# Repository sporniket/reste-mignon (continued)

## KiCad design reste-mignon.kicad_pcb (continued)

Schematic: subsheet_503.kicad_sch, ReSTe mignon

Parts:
C500, C501, C502, C511, C512, C513, C514, C523, C565: 0.1uF; C_1206_3216Metric_Pad1.33x1.80mm_HandSolder
C505, C506, C509, C510, C517, C518, C521, C522: 0.001uF; C_1206_3216Metric_Pad1.33x1.80mm_HandSolder
C2601: 0.33uF; C_1206_3216Metric_Pad1.33x1.80mm_HandSolder
CP508, CP520, CP566, CP567: 47uF; C_Radial_D6.3mm_H11.0mm_P2.50mm
CP564: 100uF; C_Radial_D8.0mm_H11.5mm_P3.50mm
Q500: UA78L08; TO-92L_Inline_Wide
R501, R502, R503, R504, R510, R511, R512, R513: 10K 1%; R_1206_3216Metric_Pad1.30x1.75mm_HandSolder
R507, R516: 1K8 1%; R_1206_3216Metric_Pad1.30x1.75mm_HandSolder
R545, R546: 100K 1%; R_1206_3216Metric_Pad1.30x1.75mm_HandSolder
U504, U507: LF347N_mu; DIP-14_W7.62mm_LongPads
U505, U506: MF4CN-100_PHY; DIP-8_W7.62mm_LongPads

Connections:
+8.2V: C500.1, C565.1, CP564.1, Q500.1 (VO), U504.4 (V+); also elsewhere on the board
/U504~~U507 — Sound amp. & filter/+12V: C2601.1, Q500.3 (VI)
ASOUND_LEFT: CP508.1; also elsewhere on the board
ASOUND_RIGHT: CP520.1; also elsewhere on the board
DAC_LEFT: U504.3 (IN1+); also elsewhere on the board
DAC_RIGHT: U504.12 (IN4+); also elsewhere on the board
FCLK: U505.2 (CLK_R), U506.2 (CLK_R); also elsewhere on the board
GIL: R507.2; also elsewhere on the board
GIR: R516.2; also elsewhere on the board
GND: C500.2, C501.2, C502.2, C509.2, C510.2, C511.1, C512.1, C513.1, C514.2, C521.2, C522.2, C523.1, C565.2, C2601.2, CP564.2, Q500.2 (GND), R545.2, R546.2, U505.3 (L.Sh), U505.6 (AGND), U506.3 (L.Sh), U506.6 (AGND), U507.3 (IN1+), U507.5 (IN2+), U507.10 (IN3+), U507.12 (IN4+); also elsewhere on the board
unnamed: CP566.1, U504.1 (OUT1), U504.2 (IN1-)
unnamed: CP567.1, U504.13 (IN4-), U504.14 (OUT4)
unnamed: CP566.2, R545.1, U505.8 (FILTER_IN)
unnamed: R503.2, U505.5 (FILTER_OUT)
unnamed: CP567.2, R546.1, U506.8 (FILTER_IN)
unnamed: R512.2, U506.5 (FILTER_OUT)
unnamed: C505.2, C509.1, R501.2, R503.1, U507.2 (IN1-)
unnamed: C505.1, R501.1, R504.2, U507.1 (OUT1)
unnamed: C517.2, C521.1, R510.2, R512.1, U507.6 (IN2-)
unnamed: C517.1, R510.1, R513.2, U507.7 (OUT2)
unnamed: C518.2, C522.1, R511.2, R513.1, R516.1, U507.9 (IN3-)
unnamed: C518.1, CP520.2, R511.1, U507.8 (OUT3)
unnamed: C506.2, C510.1, R502.2, R504.1, R507.1, U507.13 (IN4-)
unnamed: C506.1, CP508.2, R502.1, U507.14 (OUT4)
V_AUD+: C501.1, C502.1, C514.1, U505.7 (V+), U506.7 (V+), U507.4 (V+); also elsewhere on the board
V_AUD-: C511.2, C512.2, C513.2, C523.2, U504.11 (V-), U505.4 (V-), U506.4 (V-), U507.11 (V-); also elsewhere on the board

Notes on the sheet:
Use 1% resistors
Alternatives for Q500, TO-92-3 : STMicroelectronics L78L08 / Onsemi MC78L08 / Texas instrument UA78L08
for U507
for U504
for U505
for U506
Ground plane this area

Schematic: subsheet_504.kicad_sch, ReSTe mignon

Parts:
C524, C536: 0.1uF; C_1206_3216Metric_Pad1.33x1.80mm_HandSolder
C528, C531, C534, C538: 0.0082uF; C_1206_3216Metric_Pad1.33x1.80mm_HandSolder
CP525, CP529, CP535, CP537, CP541, CP543, CP544, CP546, CP547: 47uF; C_Radial_D6.3mm_H11.0mm_P2.50mm
CP542: 10uF; C_Radial_D5.0mm_H11.0mm_P2.00mm
J502: Phono LEFT; socket-rca-5-pins
J503: Phono RIGHT; socket-rca-5-pins
R520, R533, R540, R541: 1K; R_1206_3216Metric_Pad1.30x1.75mm_HandSolder
R524, R537: 3K6; R_1206_3216Metric_Pad1.30x1.75mm_HandSolder
R525, R527, R530, R538, R2701: 10K; R_1206_3216Metric_Pad1.30x1.75mm_HandSolder
R531, R539: 51K; R_1206_3216Metric_Pad1.30x1.75mm_HandSolder
R590, R591: 270K; R_1206_3216Metric_Pad1.30x1.75mm_HandSolder
U504: LF347N_mu; DIP-14_W7.62mm_LongPads
U508: LMC1992CCN_PHY; DIP-28_W15.24mm_LongPads

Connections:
+8.2V: C524.1, R525.1, U508.28 (V+); also elsewhere on the board
/U508 — Sound mix and output/audio_full: CP541.1, CP546.1, R531.1, U508.4 (LEFT_INPUT1), U508.26 (RIGHT_INPUT1)
/U508 — Sound mix and output/audio_low: R525.2, R531.2, R539.2, R2701.1, U508.5 (LEFT_INPUT2), U508.25 (RIGHT_INPUT2)
/U508 — Sound mix and output/left_op_amp_out: C531.1, U508.12 (LEFT_OP_AMP_OUT)
/U508 — Sound mix and output/left_tone_out: C531.2, U508.11 (LEFT_TONE_OUT)
/U508 — Sound mix and output/right_op_amp_out: C534.1, U508.18 (RIGHT_OP_AMP_OUT)
/U508 — Sound mix and output/right_tone_out: C534.2, U508.19 (RIGHT_TONE_OUT)
ASOUND_LEFT: C528.1, U508.9 (LEFT_SELECT_IN); also elsewhere on the board
ASOUND_RIGHT: C538.1, U508.21 (RIGHT_SELECT_IN); also elsewhere on the board
AUDIO: R540.1, R541.1; also elsewhere on the board
AUDIOI: CP546.2; also elsewhere on the board
AUDIOS: CP541.2; also elsewhere on the board
GIL: CP544.2; also elsewhere on the board
GIR: CP547.2; also elsewhere on the board
GND: C524.2, C536.2, CP535.2, CP542.2, J502.2 (Ext), J503.2 (Ext), R530.2, R590.2, R591.2, U504.5 (IN2+), U504.10 (IN3+), U508.15 (GND); also elsewhere on the board
MWD: U508.1 (DATA); also elsewhere on the board
MWK: U508.2 (CLOCK); also elsewhere on the board
unnamed: C536.1, CP535.1, R530.1, R539.1, R2701.2
unnamed: CP525.1, R520.1
unnamed: CP529.2, R527.2
unnamed: CP537.1, R533.1
unnamed: CP543.2, R538.2
unnamed: CP525.2, J502.1 (In), R590.1
unnamed: CP537.2, J503.1 (In), R591.1
unnamed: R524.2, R527.1, U504.6 (IN2-)
unnamed: R524.1, R540.2, U504.7 (OUT2)
unnamed: R537.2, R538.1, U504.9 (IN3-)
unnamed: R537.1, R541.2, U504.8 (OUT3)
unnamed: CP542.1, U508.27 (BYPASS)
unnamed: CP529.1, R520.2, U508.14 (LEFT_FRONT_OUT)
unnamed: CP544.1, U508.8 (LEFT_SELECT_OUT)
unnamed: C528.2, U508.10 (LEFT_TONE_IN)
unnamed: CP543.1, R533.2, U508.16 (RIGHT_FRONT_OUT)
unnamed: CP547.1, U508.22 (RIGHT_SELECT_OUT)
unnamed: C538.2, U508.20 (RIGHT_TONE_IN)
XMWE: U508.3 (~ENABLE); also elsewhere on the board

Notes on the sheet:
To Video port
Ground plane this area
From Video port
From YM2149
LMC Mixer Fix The original circuit gives no sound at 'audio_low', instead of a -12 dB attenuated sound to have a balanced mix of digitized sound and sound from YM2149. Peter Putnik did some research on that problem and proposed the following fix : - Cut between R531 and R539/R530, to insert a 10K r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

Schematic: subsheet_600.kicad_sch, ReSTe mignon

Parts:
C633, C634, C635, C636: 0.22uF; C_1206_3216Metric_Pad1.33x1.80mm_HandSolder
CP600: 100uF; C_Radial_D8.0mm_H11.5mm_P3.50mm
U600, U601, U602, U603: SIMM_30_PHY; socket-simm-30-P2.54mm

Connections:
GND: C633.2, C634.2, C635.2, C636.2, CP600.2, U600.9 (GND), U600.22 (GND), U601.9 (GND), U601.22 (GND), U602.9 (GND), U602.22 (GND), U603.9 (GND), U603.22 (GND); also elsewhere on the board
MADDR0: U600.4 (A0), U601.4 (A0), U602.4 (A0), U603.4 (A0); also elsewhere on the board
MADDR1: U600.5 (A1), U601.5 (A1), U602.5 (A1), U603.5 (A1); also elsewhere on the board
MADDR2: U600.7 (A2), U601.7 (A2), U602.7 (A2), U603.7 (A2); also elsewhere on the board
MADDR3: U600.8 (A3), U601.8 (A3), U602.8 (A3), U603.8 (A3); also elsewhere on the board
MADDR4: U600.11 (A4), U601.11 (A4), U602.11 (A4), U603.11 (A4); also elsewhere on the board
MADDR5: U600.12 (A5), U601.12 (A5), U602.12 (A5), U603.12 (A5); also elsewhere on the board
MADDR6: U600.14 (A6), U601.14 (A6), U602.14 (A6), U603.14 (A6); also elsewhere on the board
MADDR7: U600.15 (A7), U601.15 (A7), U602.15 (A7), U603.15 (A7); also elsewhere on the board
MADDR8: U600.17 (A8), U601.17 (A8), U602.17 (A8), U603.17 (A8); also elsewhere on the board
MADDR9: U600.18 (A9), U601.18 (A9), U602.18 (A9), U603.18 (A9); also elsewhere on the board
MDATA0: U601.3 (DQ0), U603.3 (DQ0); also elsewhere on the board
MDATA1: U601.6 (DQ1), U603.6 (DQ1); also elsewhere on the board
MDATA2: U601.10 (DQ2), U603.10 (DQ2); also elsewhere on the board
MDATA3: U601.13 (DQ3), U603.13 (DQ3); also elsewhere on the board
MDATA4: U601.16 (DQ4), U603.16 (DQ4); also elsewhere on the board
MDATA5: U601.20 (DQ5), U603.20 (DQ5); also elsewhere on the board
MDATA6: U601.23 (DQ6), U603.23 (DQ6); also elsewhere on the board
MDATA7: U601.25 (DQ7), U603.25 (DQ7); also elsewhere on the board
MDATA8: U600.3 (DQ0), U602.3 (DQ0); also elsewhere on the board
MDATA9: U600.6 (DQ1), U602.6 (DQ1); also elsewhere on the board
MDATA10: U600.10 (DQ2), U602.10 (DQ2); also elsewhere on the board
MDATA11: U600.13 (DQ3), U602.13 (DQ3); also elsewhere on the board
MDATA12: U600.16 (DQ4), U602.16 (DQ4); also elsewhere on the board
MDATA13: U600.20 (DQ5), U602.20 (DQ5); also elsewhere on the board
MDATA14: U600.23 (DQ6), U602.23 (DQ6); also elsewhere on the board
MDATA15: U600.25 (DQ7), U602.25 (DQ7); also elsewhere on the board
VCC: C633.1, C634.1, C635.1, C636.1, CP600.1, U600.1 (VCC), U600.30 (VCC), U601.1 (VCC), U601.30 (VCC), U602.1 (VCC), U602.30 (VCC), U603.1 (VCC), U603.30 (VCC); also elsewhere on the board
XCAS0H: U600.2 (~CAS); also elsewhere on the board
XCAS0L: U601.2 (~CAS); also elsewhere on the board
XCAS1H: U602.2 (~CAS); also elsewhere on the board
XCAS1L: U603.2 (~CAS); also elsewhere on the board
XRAS0: U600.27 (~RAS), U601.27 (~RAS); also elsewhere on the board
XRAS1: U602.27 (~RAS), U603.27 (~RAS); also elsewhere on the board
XWE: U600.21 (~WE), U601.21 (~WE), U602.21 (~WE), U603.21 (~WE); also elsewhere on the board

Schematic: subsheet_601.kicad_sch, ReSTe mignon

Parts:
C632: 0.1uF; C_1206_3216Metric_Pad1.33x1.80mm_HandSolder
E0, E1, E2, E3, E4, E5, E6, E7: SolderJumper_2_Open; SolderJumper-2_P1.3mm_Open_Pad1.0x1.5mm
RN2901, RN2902: 10K ×4; R_Array_Convex_4x0603
U632: 74LS244_PHY; DIP-20_W7.62mm_LongPads

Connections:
/E[0..7] — Jumper pads/e0: E0.2 (B), RN2901.1 (R1.1), U632.2 (1A1)
/E[0..7] — Jumper pads/e1: E1.2 (B), RN2901.2 (R2.1), U632.17 (2A4)
/E[0..7] — Jumper pads/e2: E2.2 (B), RN2901.3 (R3.1), U632.4 (1A2)
/E[0..7] — Jumper pads/e3: E3.2 (B), RN2901.4 (R4.1), U632.15 (2A3)
/E[0..7] — Jumper pads/e4: E4.2 (B), RN2902.1 (R1.1), U632.6 (1A3)
/E[0..7] — Jumper pads/e5: E5.2 (B), RN2902.2 (R2.1), U632.13 (2A2)
/E[0..7] — Jumper pads/e6: E6.2 (B), RN2902.3 (R3.1), U632.8 (1A4)
/E[0..7] — Jumper pads/e7: E7.2 (B), RN2902.4 (R4.1), U632.11 (2A1)
DATA8: U632.18 (1Y1); also elsewhere on the board
DATA9: U632.3 (2Y4); also elsewhere on the board
DATA10: U632.16 (1Y2); also elsewhere on the board
DATA11: U632.5 (2Y3); also elsewhere on the board
DATA12: U632.14 (1Y3); also elsewhere on the board
DATA13: U632.7 (2Y2); also elsewhere on the board
DATA14: U632.12 (1Y4); also elsewhere on the board
DATA15: U632.9 (2Y1); also elsewhere on the board
GND: C632.2, E0.1 (A), E1.1 (A), E2.1 (A), E3.1 (A), E4.1 (A), E5.1 (A), E6.1 (A), E7.1 (A), U632.10 (GND); also elsewhere on the board
VCC: C632.1, RN2901.5 (R4.2), RN2901.6 (R3.2), RN2901.7 (R2.2), RN2901.8 (R1.2), RN2902.5 (R4.2), RN2902.6 (R3.2), RN2902.7 (R2.2), RN2902.8 (R1.2), U632.20 (Vcc); also elsewhere on the board
XBUTTON: U632.1 (~1G), U632.19 (~2G); also elsewhere on the board

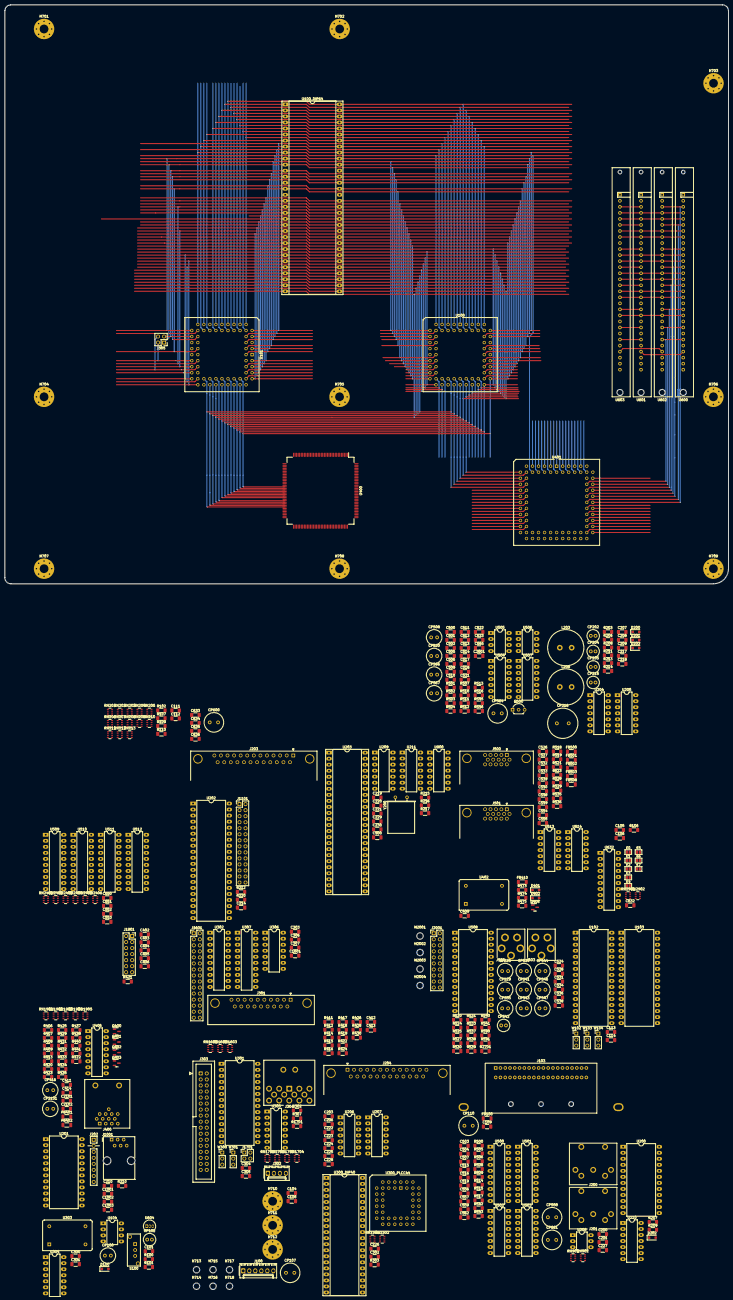
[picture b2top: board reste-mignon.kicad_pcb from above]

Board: 4 copper layers, 304.8 x 243.8 mm, 420 parts (0 on the bottom side), 492 nets.

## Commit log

2021-12-06 Removed T-filters
2021-12-08 Added DIP-64 CPU port extension
2021-12-09 removed the external blitter
2021-12-09 prepare to work publicly
2021-12-10 Resolves #1 : Use 4-resistor packs wherever it is possible
2021-12-21 annotate resistor networks and mark unused pins as unconnected
2021-12-21 Resolves #10 : Remove the C103
2021-12-21 Resolves #6 : Apply the reset fix
2021-12-21 Resolves #5 : Apply the fix for the video ghosting
2022-01-10 Resolves #7 : Assign SMD footprints to resistors pack
2022-01-11 Resolves #11 : Use the reference 'FB?' for the ferrite beads
2022-01-11 Resolves #12 : Use the reference 'CP?' for polarized capacitors
2022-02-09 Resolves #2 : apply the pull-up fix to data and address bus
2022-02-09 Resolves #3 : Apply the DMA Pull up fix on databus
2022-02-10 Resolves #4 : Apply the 1772 pull-up fix
2022-02-15 Resolves #18 : Apply the LMC mixer fix
2022-02-15 rename files as 'reste-mignon'
2022-02-16 Resolves #13 : assign 1206 hand-solder footprints to resistors
2022-02-16 Resolves #8 : Assign 1206 hand-solder footprints to non polarized capacitors
2022-03-16 Resolves #20 : Replace polarized capacitors CP101 and CP536 by unpolarized ones
2022-03-16 Resolves #9 : Assign radial THT footprints to polarized capacitors
2022-03-16 Resolves #14 : assign smd footprints for ferrite beads
2022-04-01 Resolves #16 : assign smd footprints to diodes
2022-04-01 Resolves #17 : assign smd footprints to transistors
2022-04-01 Resolves #21 : Change Q400 to Q405 from 2N3904 to MMBT3904
2022-04-01 Resolves #22 : Change Q500 from LM78L82 to UA78L08 -- add bypass capacitor on input
2022-06-02 Resolves #15 : assign smd footprints to the inductors
2022-06-02 Resolves #23 : Add internal ACSI port
2022-06-03 Resolves #24 : Add an internal port to make easier to plug a RGB2HDMI
2022-06-08 Fixes #19 : Reinstate the external blitter for the mark 0 version
2022-06-08 Prepare the schematics-only release
2022-06-08 Prepare next release
2022-06-08 Fixes #28 : [BUG] Incomplete restoration of the blitter
2022-06-08 Prepare next release (previous one was aborted because of #28)
2022-06-23 Resolves #33 : Make the WD1772 pull-up fix optionnal
2022-06-23 Rework the page design : the project url is in a comment, update the date
2022-07-10 fixed footprint for DIP-64 socket : 900 mils wide, not 600 mils
2022-07-13 Resolves #31 : Provision mounting holes of the mother board to a chassis
2022-07-13 Resolves #34 : Provision mounting holes for the Raspberry PI Zero (RGB2HDMI mod)
2022-07-13 Resolves #32 : Provision mounting hole for the 'dop' series of usb-c power delivery adapter
2022-07-13 Resolves #35 : [mk0] allow to choose between the legacy reset circuit and a supervisory circuit
2022-07-14 PCB : provisionnal dimensions and areas
2022-07-14 Resolves #36 : Add a RJ11 Keyboard connector
2022-07-14 modified target size to B4
2022-07-14 change wrong connector RJ11 (no shield), and missing pin header J1001
2022-07-14 Successfully placed all the component inside a B4 surface
2022-07-14 define edges
2022-07-14 change footprint to sockets, adjust cartridge + midi ports, external copper pours
2022-07-15 add internal layer to make a 4-layer pcb
2022-07-15 PCB settings, start ikbd
2022-07-15 done ikbd ports
2022-07-15 working on MIDI ports, swap connections to resistor network
2022-07-15 routing session : the acias
2022-07-15 routing session : extended joypad ports
2022-07-15 place RAM
2022-07-16 placing and routing rs-232
2022-07-16 wired parallel port
2022-07-16 start placing and wiring floppy ports
2022-07-19 START of placing video port circuits
2022-07-21 layout and trace Video port
2022-09-23 pcb session -- ven. 23 sept. 2022 23:18:20 CEST
2022-09-29 pcb session -- jeu. 29 sept. 2022 11:56:23 CEST
2022-09-29 pcb session -- jeu. 29 sept. 2022 12:30:19 CEST
2022-09-29 pcb session -- jeu. 29 sept. 2022 13:13:36 CEST
2022-09-29 pcb session -- jeu. 29 sept. 2022 19:04:06 CEST
2022-09-29 pcb session -- jeu. 29 sept. 2022 23:38:31 CEST
2022-09-30 pcb session -- ven. 30 sept. 2022 07:13:44 CEST
2022-10-22 update custom footprint : radial inductor tht, diam 15mm, pitch 5mm
2022-10-22 Resolves #39 : [mk0] Select THT power inductors for L203-L208
2022-10-23 pcb session 2022-10-23T17:53:39+02:00
2022-10-24 Fixes #40 : Q500, revert to TO-92 package and alternatives references
2022-10-25 pcb session 2022-10-25T06:21:13+02:00
2022-10-25 pcb session 2022-10-25T07:12:15+02:00 : provision space for RGB2HDMI
2022-10-25 added missing bypass capacitor for U405
2022-10-25 pcb session 2022-10-25T07:26:45+02:00
2022-10-26 adjust the rgb2hdmi connector position
2022-10-26 rework of the acia and midi positioning
2022-10-26 rework position of cpu, blitter and mcu
2022-10-28 pcb session 2022-10-28T07:23:50+02:00
2022-10-28 pcb session 2022-10-28T07:28:25+02:00
2022-10-28 Resolves #37 : [mk0] Add a breakout connector for serial and parallel signal
2022-10-28 Resolves #38 : [mk0] add a breakout connector for the MCU ROM[0..6]
2022-12-15 done placing component, require psu work and update
2022-12-15 start routing acsi
2022-12-16 pcb - session 2022-12-16T04:45:35+01:00
2022-12-16 pcb - session 2022-12-16T09:19:23+01:00
2022-12-17 pcb session -- 2022-12-17T18:55:52+01:00
2022-12-17 pcb session -- 2022-12-17T20:33:02+01:00
2022-12-17 pcb session -- 2022-12-17T21:00:52+01:00
2022-12-17 pcb session -- 2022-12-17T22:13:09+01:00
2022-12-21 pcb session -- 2022-12-21T22:35:12+01:00
2022-12-22 pcb session -- 2022-12-22T08:54:35+01:00
2022-12-22 pcb session -- 2022-12-22T18:32:53+01:00
2023-01-09 PCB session - 2023-01-09T05:11:55+01:00
2023-01-09 PCB session - 2023-01-09T06:06:22+01:00
2023-01-21 pcb session 2023-01-09 22:28
2023-01-21 MIGRATION TO KICAD 6 !
2023-01-21 pcb session 2023-01-21T07:55:41+01:00
2023-01-21 pcb session 2023-01-21T19:17:59+01:00
2023-01-21 pcb session 2023-01-21T22:41:51+01:00
2023-01-22 pcb session 2023-01-22T07:00:41+01:00
2023-01-23 add gnd/vcc symbol to start replacing local labels
2023-01-23 connect vcc/gnd, pp 28,29
2023-01-23 replace symbol Device:CP1 by Device:C_Polarized_US
2023-11-20 backup 2023-11-20T20:35:01+01:00
2023-11-20 convert to Kicad 7
2023-11-20 cleanstep : remove kicad 5 files
2023-11-20 Reset pcb, draws ATX guidelines
2023-11-20 interconnect 68k sockets (dip and plcc)
2023-11-21 pcb session 2023-11-21T04:54:50+01:00 : position blitter, mounting holes
2023-11-21 pcb session 2023-11-21T05:51:32+01:00 : routing blitter north and south sides
2023-11-22 pcb session 2023-11-22T23:13:50+01:00 -- place RAM, shifter and MCU
2024-06-10 start specifying CPU + blitter extension connector
2024-06-11 complete specification of CPU + blitter extension connector
2024-06-11 renamed specification file of cpu + blitter extension port
2024-06-13 added new library of symbols to have CPU connector A and B
2024-06-16 cpu and blitter extension port -- specify how it is wired on mainboard and extensions
2024-06-20 Fixes extension port cpu Connector B -- pinout
2024-06-20 ad-hoc symbols for extension port cpu and blitter connectors
2024-06-20 create project
2024-06-20 Setup metadata, starting schematic
2024-06-21 done main wiring, remaining pull-ups
2024-06-22 done schematic
2024-06-22 done footprint association, DRC
2024-06-22 pcb session -- laying out component -- fixed footprint associations
2024-06-22 pcb session -- change cpu orientation for easier routing
2024-06-22 pcb session -- start wiring
2024-06-23 pcb session -- start pull-ups, adjust pull-up mapping of RN1 for ease of routing
2024-06-23 pcb session -- continue pull-ups, done a1-a12
2024-06-23 pcb session -- switch to 4 layers, spread vias to avoid cuts in ground plane
2024-06-23 pcb session -- done the address bus a1~a23
2024-06-23 switch RN5 and RN6 to ease routing
2024-06-23 pcb session -- adjust constraints to pass drc, silkscreen -- start using free angles
2024-06-23 pcb session -- done using free angles -- good enough to order
2024-06-24 pcb session -- adding measurements -- some more free angles
2024-06-24 pcb session -- tweaks angles here and there
2024-06-25 scripted gerber generation (not to be in ci)
2024-06-26 pcb session -- replicate most marking onto the back silkscreen
2024-06-26 pcb session -- tweak traces again for better regularity, fix copper pour for ground
2024-06-27 prepare release of the extension cpu
2024-06-27 fix typo in README
2024-06-28 fix drill file generation
